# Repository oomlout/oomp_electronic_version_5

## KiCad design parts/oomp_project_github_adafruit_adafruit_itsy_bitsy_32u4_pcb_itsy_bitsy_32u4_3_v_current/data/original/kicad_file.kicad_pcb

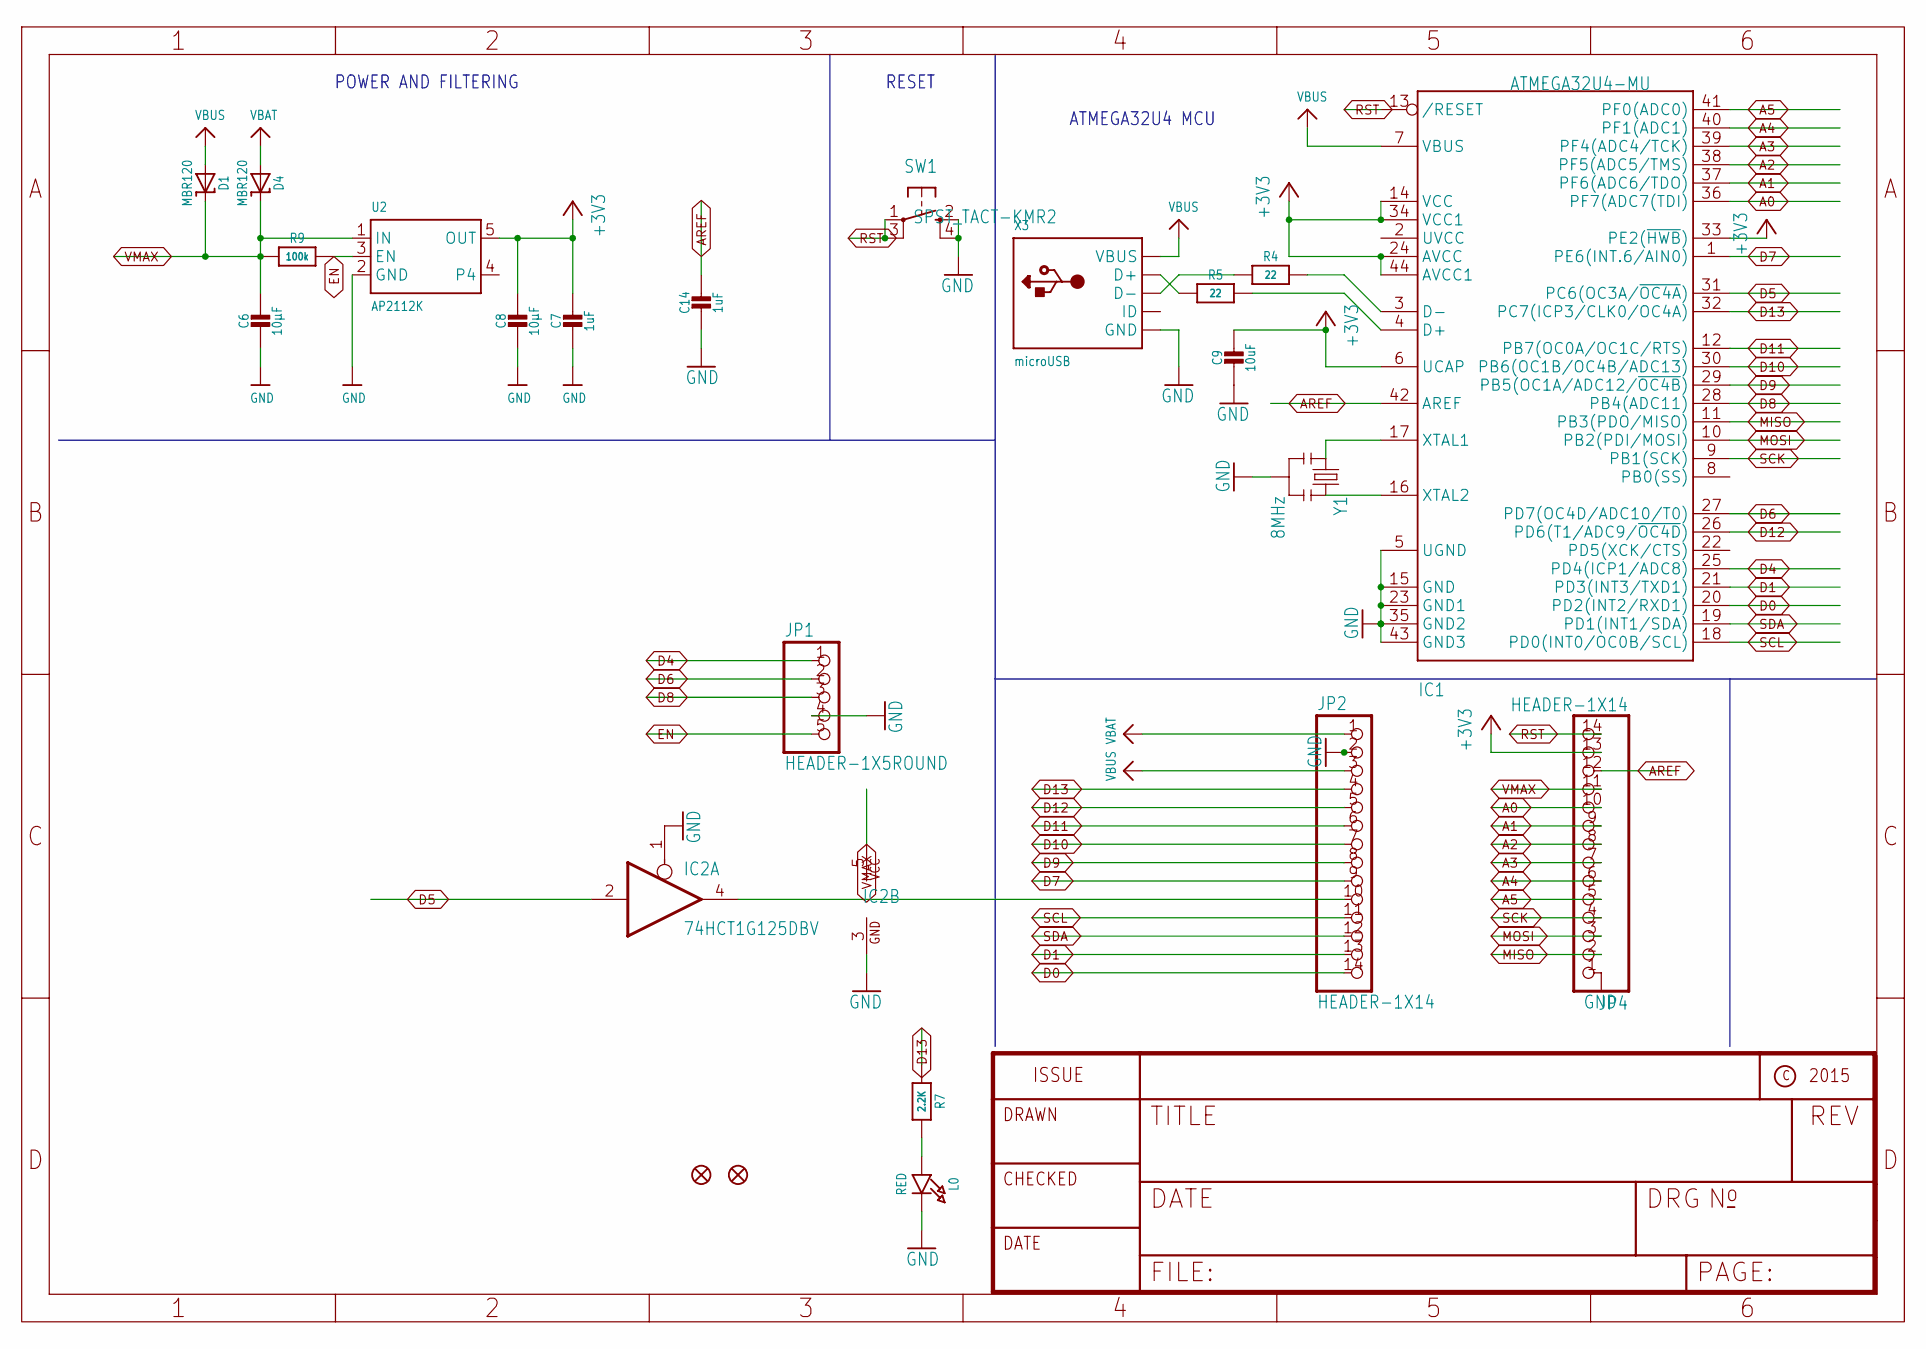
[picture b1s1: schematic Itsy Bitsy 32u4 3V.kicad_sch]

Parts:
C6, C8: 10µF; 0805-NO
C7, C14: 1uF; 0603-NO
C9: 10uF; 0805-NO
D1, D4: MBR120; SOD-123
IC1: ATMEGA32U4-MU; TQFN44_7MM
IC2: 74HCT1G125DBV; SOT23-5
JP1: HEADER-1X5ROUND; 1X05_ROUND
JP2, JP4: HEADER-1X14; 1X14_ROUND70
L0: RED; CHIPLED_0805_NOOUTLINE
R4, R5: 22; 0603-NO
R7: 2.2K; 0603-NO
R9: 100k; 0603-NO
SW1: SPST_TACT-KMR2; KMR2
U2: AP2112K; SOT23-5
U$34, U$35: FIDUCIAL""; FIDUCIAL_1MM
X3: microUSB; 4UCONN_20329_V2
Y1: 8MHz; RESONATOR-SMD

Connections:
+3V3: C7.1, C8.1, C9.1, IC1.6 (UCAP), IC1.14 (VCC), IC1.24 (AVCC), IC1.33 (PE2(~HWB)), IC1.34 (VCC1), IC1.44 (AVCC1), JP4.13, U2.5 (OUT)
A0: IC1.36 (PF7(ADC7(TDI)), JP4.10
A1: IC1.37 (PF6(ADC6/TDO)), JP4.9
A2: IC1.38 (PF5(ADC5/TMS)), JP4.8
A3: IC1.39 (PF4(ADC4/TCK)), JP4.7
A4: IC1.40 (PF1(ADC1)), JP4.6
A5: IC1.41 (PF0(ADC0)), JP4.5
AREF: C14.1, IC1.42 (AREF), JP4.12
D0: IC1.20 (PD2(INT2/RXD1)), JP2.14
D1: IC1.21 (PD3(INT3/TXD1)), JP2.13
D4: IC1.25 (PD4(ICP1/ADC8)), JP1.1
D5: IC1.31 (PC6(OC3A/~OC4A)), IC2.2 (I)
D5_OUT: IC2.4 (O), JP2.10
D6: IC1.27 (PD7(OC4D/ADC10/T0)), JP1.2
D7: IC1.1 (PE6(INT.6/AIN0)), JP2.9
D8: IC1.28 (PB4(ADC11)), JP1.3
D9: IC1.29 (PB5(OC1A/ADC12/~OC4B)), JP2.8
D10: IC1.30 (PB6(OC1B/OC4B/ADC13)), JP2.7
D11: IC1.12 (PB7(OC0A/OC1C/RTS)), JP2.6
D12: IC1.26 (PD6(T1/ADC9/~OC4D)), JP2.5
D13: IC1.32 (PC7(ICP3/CLK0/OC4A)), JP2.4, R7.1
D+: IC1.4 (D+), R5.2
D-: IC1.3 (D-), R4.2
EN: JP1.5, R9.2, U2.3 (EN)
GND: C6.2, C7.2, C8.2, C9.2, C14.2, IC1.5 (UGND), IC1.15 (GND), IC1.23 (GND1), IC1.35 (GND2), IC1.43 (GND3), IC2.1 (OE), IC2.3 (GND), JP1.4, JP2.2, JP4.1, L0.C, SW1.2 (S), SW1.4 (S1), U2.2 (GND), X3.BASE@1 (GND), X3.BASE@2 (GND), X3.GND, X3.SPRT@1 (GND), X3.SPRT@2 (GND), X3.SPRT@3 (GND), X3.SPRT@4 (GND), Y1.2
MISO: IC1.11 (PB3(PDO/MISO)), JP4.2
MOSI: IC1.10 (PB2(PDI/MOSI)), JP4.3
unnamed: L0.A, R7.2
unnamed: IC1.16 (XTAL2), Y1.3
unnamed: IC1.17 (XTAL1), Y1.1
unnamed: R5.1, X3.D+
unnamed: R4.1, X3.D-
RST: IC1.13 (/RESET), JP4.14, SW1.1, SW1.3 (P1)
SCK: IC1.9 (PB1(SCK)), JP4.4
SCL: IC1.18 (PD0(INT0/OC0B/SCL)), JP2.11
SDA: IC1.19 (PD1(INT1/SDA)), JP2.12
VBAT: D4.A, JP2.1
VBUS: D1.A, IC1.7 (VBUS), JP2.3, X3.VBUS
VMAX: C6.1, D1.C, D4.C, IC2.5 (VCC), JP4.11, R9.1, U2.1 (IN)

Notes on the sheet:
POWER AND FILTERING
RESET
ATMEGA32U4 MCU

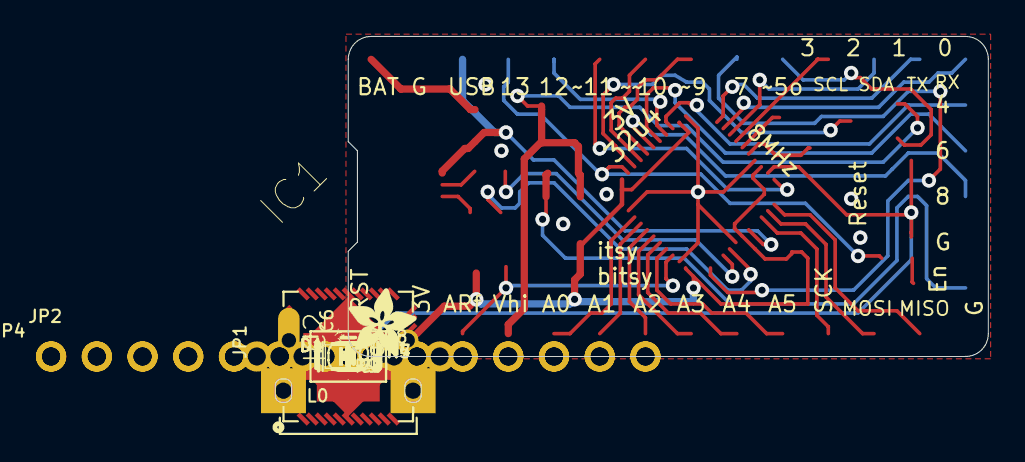
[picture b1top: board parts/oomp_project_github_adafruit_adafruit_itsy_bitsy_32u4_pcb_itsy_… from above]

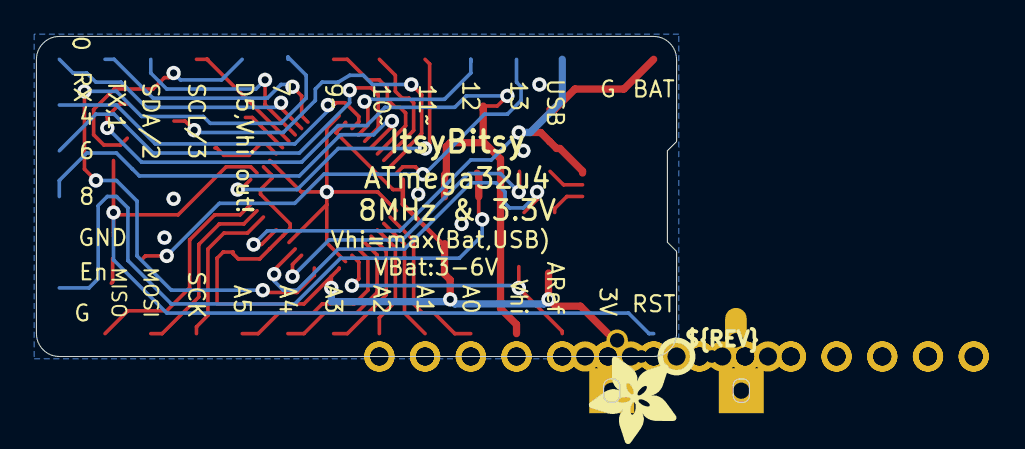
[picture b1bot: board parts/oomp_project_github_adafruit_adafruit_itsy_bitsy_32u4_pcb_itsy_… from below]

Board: 2 copper layers, 35.6 x 17.8 mm, 26 parts (2 on the bottom side), 39 nets.

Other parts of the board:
U$2: PCBFEAT-REV-040
U$4: ADAFRUIT_5MM
U$7: ADAFRUIT_3.5MM

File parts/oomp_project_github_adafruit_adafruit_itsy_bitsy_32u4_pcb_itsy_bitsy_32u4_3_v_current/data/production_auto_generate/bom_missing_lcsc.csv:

Designator,Comment,Footprint,OOMP ID,Reason
C6,10µF,Itsy Bitsy 32u4 3V-import-fps:0805-NO,electronic_capacitor_0805_10_micro_farad,No verified LCSC part number
C8,10µF,Itsy Bitsy 32u4 3V-import-fps:0805-NO,electronic_capacitor_0805_10_micro_farad,No verified LCSC part number
C9,10uF,Itsy Bitsy 32u4 3V-import-fps:0805-NO,electronic_capacitor_0805_10_micro_farad,No verified LCSC part number
D1,MBR120,Itsy Bitsy 32u4 3V-import-fps:SOD-123,,No verified LCSC part number
D4,MBR120,Itsy Bitsy 32u4 3V-import-fps:SOD-123,,No verified LCSC part number
IC1,ATMEGA32U4-MU,Itsy Bitsy 32u4 3V-import-fps:TQFN44_7MM,,No verified LCSC part number
IC2,74HCT1G125DBV,Itsy Bitsy 32u4 3V-import-fps:SOT23-5,,No verified LCSC part number
L0,RED,Itsy Bitsy 32u4 3V-import-fps:CHIPLED_0805_NOOUTLINE,electronic_led_0805_red,No verified LCSC part number
SW1,SPST_TACT-KMR2,Itsy Bitsy 32u4 3V-import-fps:KMR2,,No verified LCSC part number
U2,AP2112K,Itsy Bitsy 32u4 3V-import-fps:SOT23-5,,No verified LCSC part number
U$2,,Itsy Bitsy 32u4 3V-import-fps:PCBFEAT-REV-040,,No verified LCSC part number
U$4,,Itsy Bitsy 32u4 3V-import-fps:ADAFRUIT_5MM,,No verified LCSC part number
U$7,,Itsy Bitsy 32u4 3V-import-fps:ADAFRUIT_3.5MM,,No verified LCSC part number
U$34,"FIDUCIAL""""",Itsy Bitsy 32u4 3V-import-fps:FIDUCIAL_1MM,,No verified LCSC part number
U$35,"FIDUCIAL""""",Itsy Bitsy 32u4 3V-import-fps:FIDUCIAL_1MM,,No verified LCSC part number
X3,microUSB,Itsy Bitsy 32u4 3V-import-fps:4UCONN_20329_V2,,No verified LCSC part number
Y1,8MHz,Itsy Bitsy 32u4 3V-import-fps:RESONATOR-SMD,,No verified LCSC part number

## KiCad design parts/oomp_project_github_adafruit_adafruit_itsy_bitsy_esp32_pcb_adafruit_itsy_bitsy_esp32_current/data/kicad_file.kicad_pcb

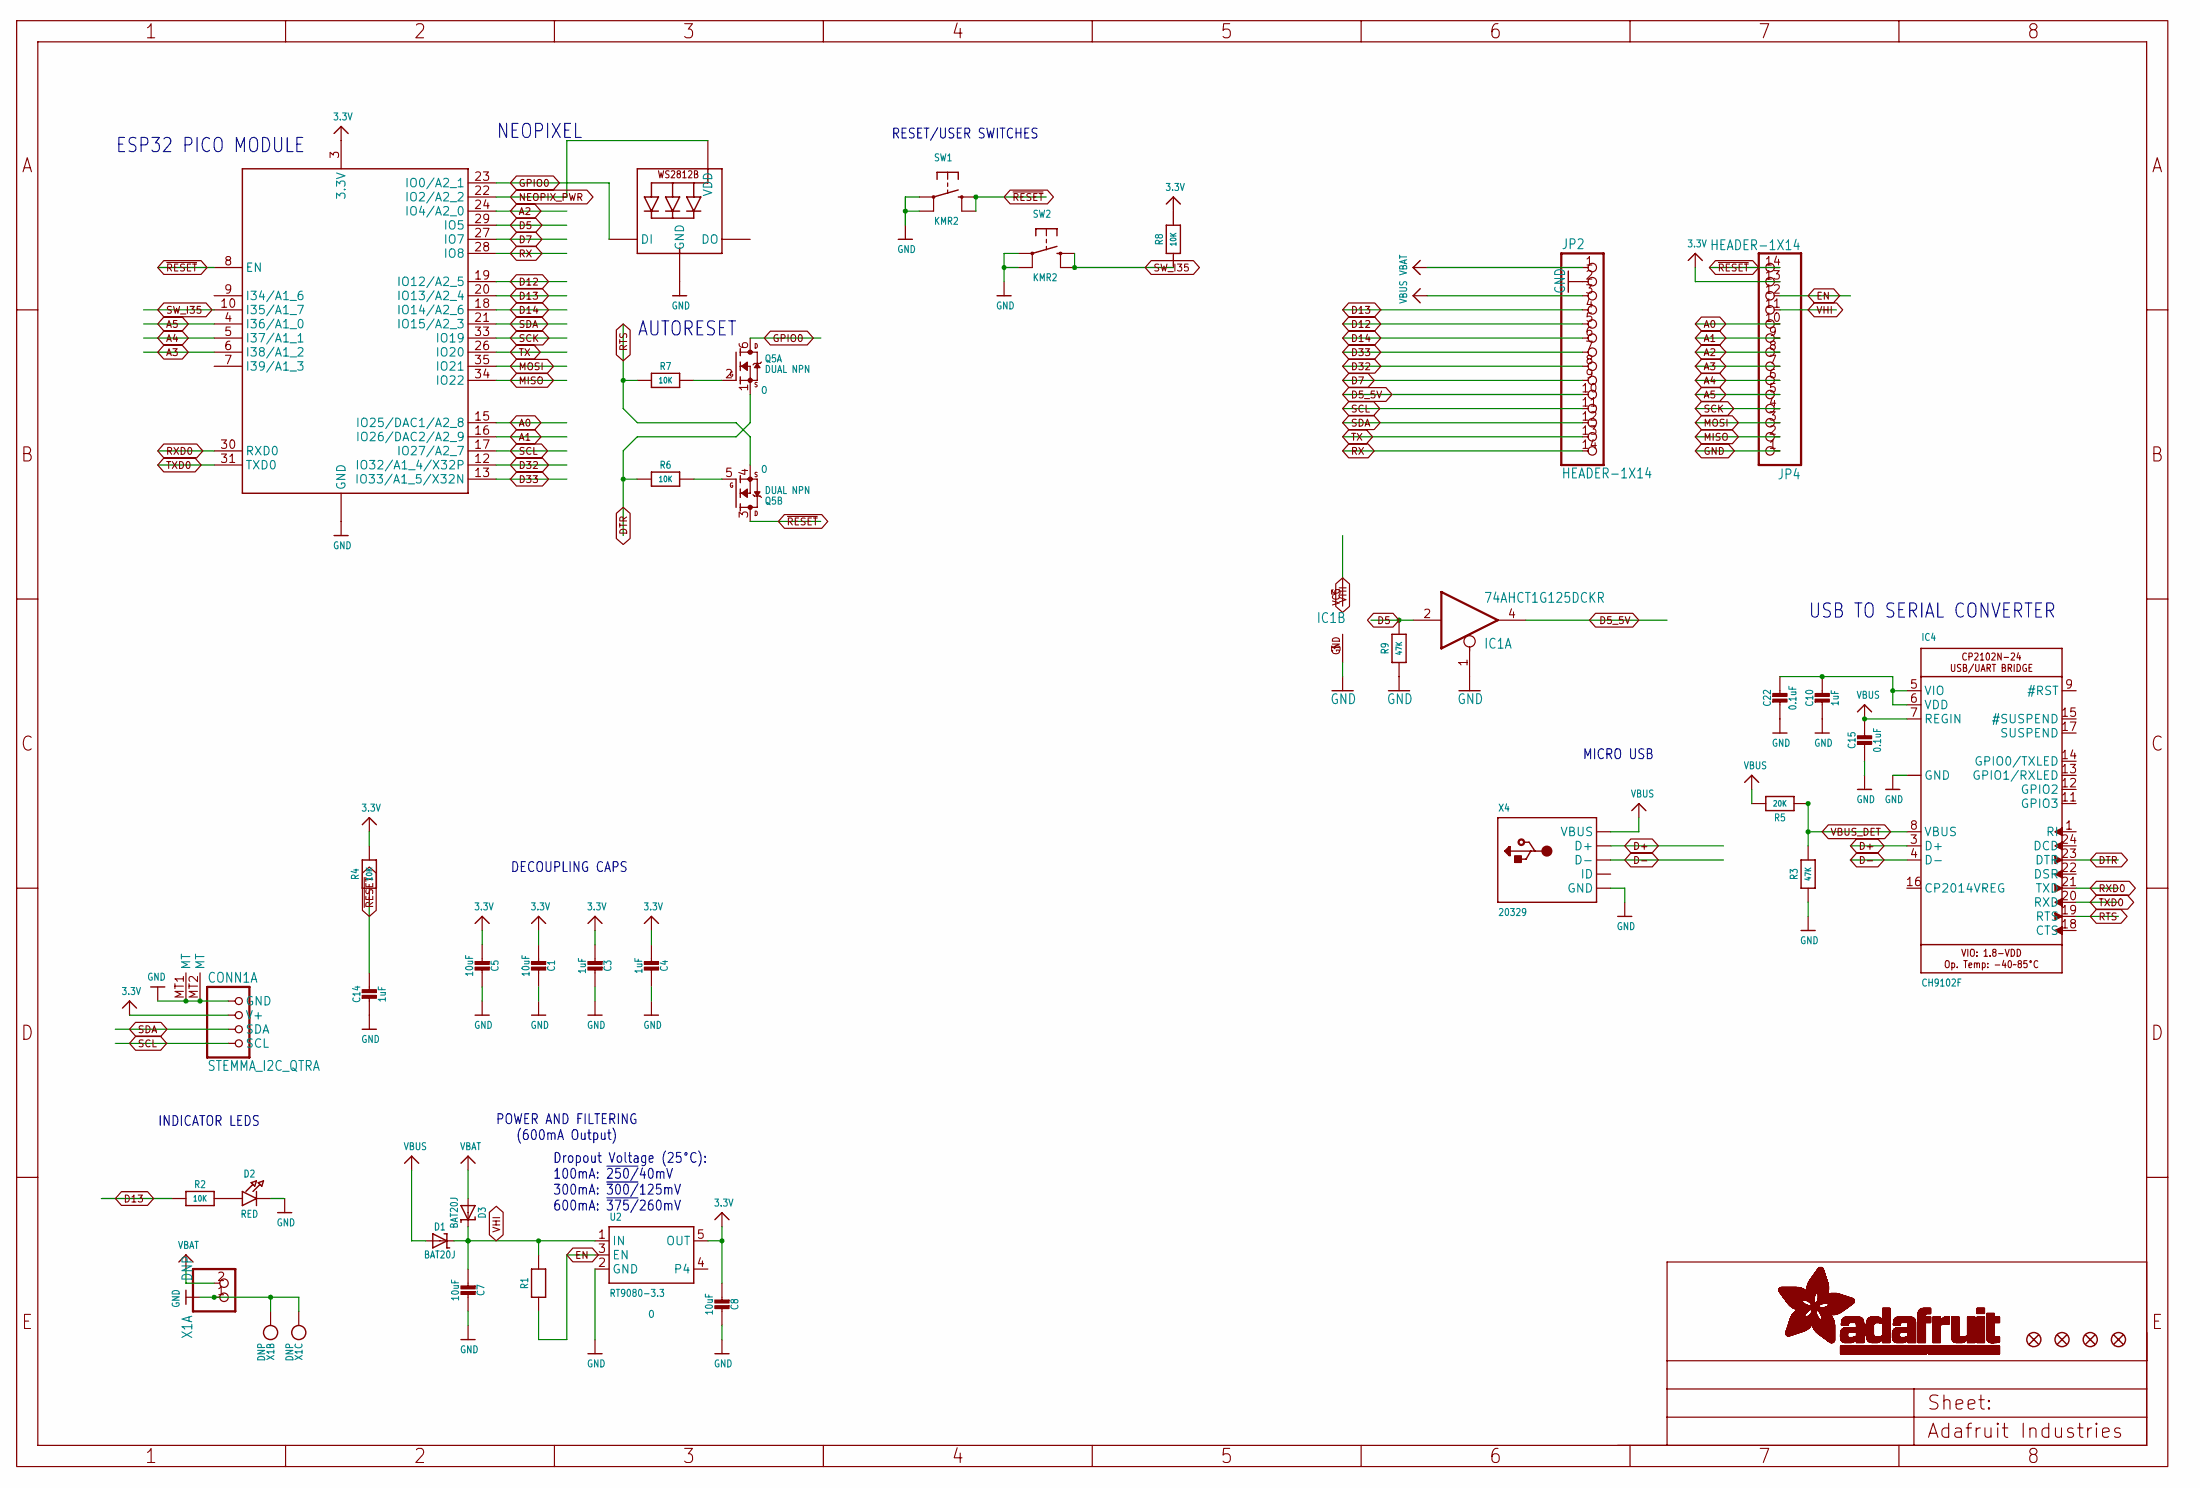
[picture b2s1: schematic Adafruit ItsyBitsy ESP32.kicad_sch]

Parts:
C1, C5, C7, C8: 10uF; 0805-NO
C3, C4, C10, C14: 1uF; 0603-NO
C15, C22: 0.1uF; 0603-NO
CONN1: STEMMA_I2C_QTRA; JST_SH4_RA; LCSC C145961
D1, D3: BAT20J; SOD-323
D2: RED; CHIPLED_0603_NOOUTLINE
FID1, FID2, FID3, FID4: FIDUCIAL_1MM
IC1: 74AHCT1G125DCKR; SC70-5
IC4: CH9102F; QFN24_4MM_SMSC; JLC_ROTATION 270
JP2, JP4: HEADER-1X14; 1X14_ROUND70
LED2: WS2812B_SK6805_1515; SK6805_1515; LCSC C2890035
Q5: DUAL NPN; SOT363; JLC_ROTATION 0
R1, R2, R4, R6, R7, R8: 10K; 0603-NO
R3, R9: 47K; 0603-NO
R5: 20K; 0603-NO
SW1, SW2: KMR2; BTN_RKB2_4.6X2.8
U2: RT9080-3.3; SOT23-5; JLC_ROTATION 0
X1: DNP; JSTPH2_BATT; LCSC C47647
X3: ESP32-PICO-MINI-02MINI; ESP32-PICO-MINI
X4: 20329; 4UCONN_20329_SLIM

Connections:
3.3V: C1.2, C3.2, C4.2, C5.2, C8.2, CONN1.2 (V+), JP4.13, R4.2, R8.2, U2.5 (OUT), X3.3 (3.3V)
3.45V: C10.1, C22.1, IC4.5 (VIO), IC4.6 (VDD)
A0: JP4.10, X3.15 (IO25/DAC1/A2_8)
A1: JP4.9, X3.16 (IO26/DAC2/A2_9)
A2: JP4.8, X3.24 (IO4/A2_0)
A3: JP4.7, X3.6 (I38/A1_2)
A4: JP4.6, X3.5 (I37/A1_1)
A5: JP4.5, X3.4 (I36/A1_0)
D5: IC1.2 (I), R9.2, X3.29 (IO5)
D5_5V: IC1.4 (O), JP2.10
D7: JP2.9, X3.27 (IO7)
D12: JP2.5, X3.19 (IO12/A2_5)
D13: JP2.4, R2.1, X3.20 (IO13/A2_4)
D14: JP2.6, X3.18 (IO14/A2_6)
D32: JP2.8, X3.12 (IO32/A1_4/X32P)
D33: JP2.7, X3.13 (IO33/A1_5/X32N)
D+: IC4.3 (D+), X4.D+
D-: IC4.4 (D-), X4.D-
DTR: IC4.23 (DTR), Q5.1 (S), R6.1
EN: JP4.12, R1.1, U2.3 (EN)
GND: C1.1, C3.1, C4.1, C5.1, C7.1, C8.1, C10.2, C14.2, C15.2, C22.2, CONN1.1 (GND), CONN1.MT1 (MT), CONN1.MT2 (MT), D2.C, IC1.1 (OE), IC1.3 (GND), IC4.2 (GND), IC4.THERM (GND), JP2.2, JP4.1, LED2.4 (GND), R3.1, R9.1, SW1.A, SW1.A' (P1), SW2.A, SW2.A' (P1), U2.2 (GND), X1.1, X1.NC1, X1.NC2, X3.1 (GND), X3.2 (GND), X3.11 (GND), X3.14 (GND), X3.36 (GND), X3.37 (GND), X3.38 (GND), X3.39 (GND), X3.40 (GND), X3.41 (GND), X3.42 (GND), X3.43 (GND), X3.44 (GND), X3.45 (GND), X3.46 (GND), X3.47 (GND), X3.48 (GND), X3.49 (GND), X3.50 (GND), X3.51 (GND), X3.52 (GND), X3.53 (GND), X3.54 (GND), X3.55 (GND), X3.56 (GND), X3.57 (GND), X3.58 (GND), X3.59 (GND), X3.60 (GND), X3.61 (GND), X4.BASE@1 (GND), X4.BASE@2 (GND), X4.GND, X4.SPRT@1 (GND), X4.SPRT@2 (GND), X4.SPRT@3 (GND), X4.SPRT@4 (GND)
GPIO0: LED2.1 (DI), Q5.6 (D), X3.23 (IO0/A2_1)
MISO: JP4.2, X3.34 (IO22)
MOSI: JP4.3, X3.35 (IO21)
unnamed: D2.A, R2.2
unnamed: Q5.5 (G), R6.2
unnamed: Q5.2 (G), R7.2
NEOPIX_PWR: LED2.2 (VDD), X3.22 (IO2/A2_2)
RTS: IC4.19 (RTS), Q5.4 (S), R7.1
RX: JP2.14, X3.28 (IO8)
RXD0: IC4.21 (TXD), X3.30 (RXD0)
SCK: JP4.4, X3.33 (IO19)
SCL: CONN1.4 (SCL), JP2.11, X3.17 (IO27/A2_7)
SDA: CONN1.3 (SDA), JP2.12, X3.21 (IO15/A2_3)
SW_I35: R8.1, SW2.B (S), SW2.B' (S1), X3.10 (I35/A1_7)
TX: JP2.13, X3.26 (IO20)
TXD0: IC4.20 (RXD), X3.31 (TXD0)
VBAT: D3.A, JP2.1, X1.2
VBUS: C15.1, D1.A, IC4.7 (REGIN), JP2.3, R5.2, X4.VBUS
VBUS_DET: IC4.8 (VBUS), R3.2, R5.1
VHI: C7.2, D1.C, D3.C, IC1.5 (VCC), JP4.11, R1.2, U2.1 (IN)
~RESET: C14.1, JP4.14, Q5.3 (D), R4.1, SW1.B (S), SW1.B' (S1), X3.8 (EN)

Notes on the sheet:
AUTORESET
MICRO USB
Dropout Voltage (25°C): 100mA: ~{250/}40mV 300mA: ~{300/}125mV 600mA: ~{375/}260mV
POWER AND FILTERING (600mA Output)
RESET/USER SWITCHES
ESP32 PICO MODULE
INDICATOR LEDS
DECOUPLING CAPS
USB TO SERIAL CONVERTER
NEOPIXEL

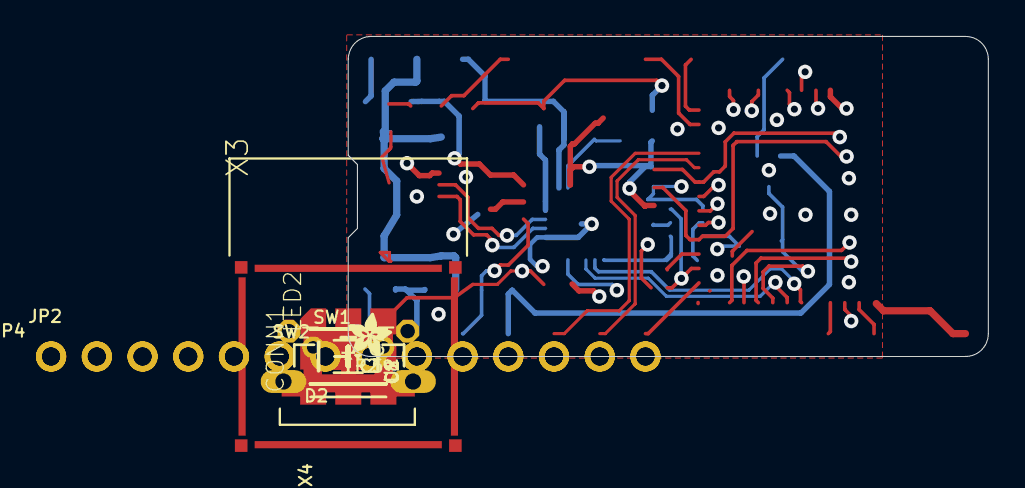
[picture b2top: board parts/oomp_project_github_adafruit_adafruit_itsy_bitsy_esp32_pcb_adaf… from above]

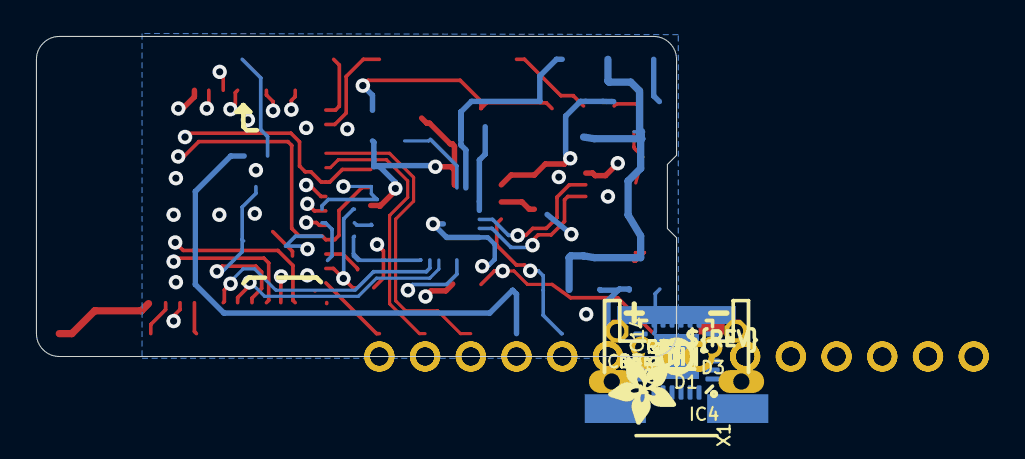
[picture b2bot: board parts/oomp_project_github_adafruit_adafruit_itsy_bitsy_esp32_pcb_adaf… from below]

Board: 4 copper layers, 35.6 x 17.8 mm, 87 parts (48 on the bottom side), 42 nets.

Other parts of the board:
E$1: ADAFRUIT_2.5MM
E$2: ADAFRUIT_3.5MM
PLABEL0: PLABEL0
PLABEL1: PLABEL1
PLABEL2: PLABEL2
PLABEL3: PLABEL3
PLABEL4: PLABEL4
PLABEL5: PLABEL5
PLABEL6: PLABEL6
PLABEL7: PLABEL7
PLABEL8: PLABEL8
PLABEL9: PLABEL9
PLABEL10: PLABEL10
PLABEL11: PLABEL11
PLABEL12: PLABEL12
PLABEL13: PLABEL13
PLABEL14: PLABEL14
PLABEL15: PLABEL15
PLABEL16: PLABEL16
PLABEL17: PLABEL17
PLABEL18: PLABEL18
PLABEL19: PLABEL19
PLABEL20: PLABEL20
PLABEL21: PLABEL21
PLABEL22: PLABEL22
PLABEL23: PLABEL23
PLABEL24: PLABEL24
PLABEL25: PLABEL25
PLABEL26: PLABEL26
PLABEL27: PLABEL27
PLABEL28: PLABEL28
PLABEL29: PLABEL29
PLABEL30: PLABEL30
PLABEL31: PLABEL31
PLABEL32: PLABEL32
PLABEL33: PLABEL33
PLABEL34: PLABEL34
PLABEL35: PLABEL35
PLABEL36: PLABEL36
PLABEL37: PLABEL37
PLABEL38: PLABEL38
PLABEL39: PLABEL39
PLABEL40: PLABEL40
PLABEL41: PLABEL41
PLABEL42: PLABEL42
PLABEL43: PLABEL43
PLABEL44: PLABEL44
U$16: PCBFEAT-REV-040

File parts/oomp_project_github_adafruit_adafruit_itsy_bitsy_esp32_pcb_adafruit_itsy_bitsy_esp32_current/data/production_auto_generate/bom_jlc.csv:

Comment,Designator,Footprint,LCSC Part #
,"JP2,JP4",Adafruit ItsyBitsy ESP32-import-fps:1X14_ROUND70,C2905490
,E$1,Adafruit ItsyBitsy ESP32-import-fps:ADAFRUIT_2.5MM,
,E$2,Adafruit ItsyBitsy ESP32-import-fps:ADAFRUIT_3.5MM,
,U$16,Adafruit ItsyBitsy ESP32-import-fps:PCBFEAT-REV-040,
,PLABEL0,Adafruit ItsyBitsy ESP32-import-fps:PLABEL0,
,PLABEL1,Adafruit ItsyBitsy ESP32-import-fps:PLABEL1,
,PLABEL10,Adafruit ItsyBitsy ESP32-import-fps:PLABEL10,
,PLABEL11,Adafruit ItsyBitsy ESP32-import-fps:PLABEL11,
,PLABEL12,Adafruit ItsyBitsy ESP32-import-fps:PLABEL12,
,PLABEL13,Adafruit ItsyBitsy ESP32-import-fps:PLABEL13,
,PLABEL14,Adafruit ItsyBitsy ESP32-import-fps:PLABEL14,
,PLABEL15,Adafruit ItsyBitsy ESP32-import-fps:PLABEL15,
,PLABEL16,Adafruit ItsyBitsy ESP32-import-fps:PLABEL16,
,PLABEL17,Adafruit ItsyBitsy ESP32-import-fps:PLABEL17,
,PLABEL18,Adafruit ItsyBitsy ESP32-import-fps:PLABEL18,
,PLABEL19,Adafruit ItsyBitsy ESP32-import-fps:PLABEL19,
,PLABEL2,Adafruit ItsyBitsy ESP32-import-fps:PLABEL2,
,PLABEL20,Adafruit ItsyBitsy ESP32-import-fps:PLABEL20,
,PLABEL21,Adafruit ItsyBitsy ESP32-import-fps:PLABEL21,
,PLABEL22,Adafruit ItsyBitsy ESP32-import-fps:PLABEL22,
,PLABEL23,Adafruit ItsyBitsy ESP32-import-fps:PLABEL23,
,PLABEL24,Adafruit ItsyBitsy ESP32-import-fps:PLABEL24,
,PLABEL25,Adafruit ItsyBitsy ESP32-import-fps:PLABEL25,
,PLABEL26,Adafruit ItsyBitsy ESP32-import-fps:PLABEL26,
,PLABEL27,Adafruit ItsyBitsy ESP32-import-fps:PLABEL27,
,PLABEL28,Adafruit ItsyBitsy ESP32-import-fps:PLABEL28,
,PLABEL29,Adafruit ItsyBitsy ESP32-import-fps:PLABEL29,
,PLABEL3,Adafruit ItsyBitsy ESP32-import-fps:PLABEL3,
,PLABEL30,Adafruit ItsyBitsy ESP32-import-fps:PLABEL30,
,PLABEL31,Adafruit ItsyBitsy ESP32-import-fps:PLABEL31,
,PLABEL32,Adafruit ItsyBitsy ESP32-import-fps:PLABEL32,
,PLABEL33,Adafruit ItsyBitsy ESP32-import-fps:PLABEL33,
,PLABEL34,Adafruit ItsyBitsy ESP32-import-fps:PLABEL34,
,PLABEL35,Adafruit ItsyBitsy ESP32-import-fps:PLABEL35,
,PLABEL36,Adafruit ItsyBitsy ESP32-import-fps:PLABEL36,
,PLABEL37,Adafruit ItsyBitsy ESP32-import-fps:PLABEL37,
,PLABEL38,Adafruit ItsyBitsy ESP32-import-fps:PLABEL38,
,PLABEL39,Adafruit ItsyBitsy ESP32-import-fps:PLABEL39,
,PLABEL4,Adafruit ItsyBitsy ESP32-import-fps:PLABEL4,
,PLABEL40,Adafruit ItsyBitsy ESP32-import-fps:PLABEL40,
,PLABEL41,Adafruit ItsyBitsy ESP32-import-fps:PLABEL41,
,PLABEL42,Adafruit ItsyBitsy ESP32-import-fps:PLABEL42,
,PLABEL43,Adafruit ItsyBitsy ESP32-import-fps:PLABEL43,
,PLABEL44,Adafruit ItsyBitsy ESP32-import-fps:PLABEL44,
,PLABEL5,Adafruit ItsyBitsy ESP32-import-fps:PLABEL5,
,PLABEL6,Adafruit ItsyBitsy ESP32-import-fps:PLABEL6,
,PLABEL7,Adafruit ItsyBitsy ESP32-import-fps:PLABEL7,
,PLABEL8,Adafruit ItsyBitsy ESP32-import-fps:PLABEL8,
,PLABEL9,Adafruit ItsyBitsy ESP32-import-fps:PLABEL9,
0.1uF,"C15,C22",Adafruit ItsyBitsy ESP32-import-fps:0603-NO,C14663
10K,"R1,R2,R4,R6,R7,R8",Adafruit ItsyBitsy ESP32-import-fps:0603-NO,C98220
10uF,"C1,C5,C7,C8",Adafruit ItsyBitsy ESP32-import-fps:0805-NO,
1uF,"C3,C4,C10,C14",Adafruit ItsyBitsy ESP32-import-fps:0603-NO,C5673
20329,X4,Adafruit ItsyBitsy ESP32-import-fps:4UCONN_20329_SLIM,
20K,R5,Adafruit ItsyBitsy ESP32-import-fps:0603-NO,
47K,"R3,R9",Adafruit ItsyBitsy ESP32-import-fps:0603-NO,C2907042
74AHCT1G125DCKR,IC1,Adafruit ItsyBitsy ESP32-import-fps:SC70-5,
BAT20J,"D1,D3",Adafruit ItsyBitsy ESP32-import-fps:SOD-323,
CH9102F,IC4,Adafruit ItsyBitsy ESP32-import-fps:QFN24_4MM_SMSC,
DNP,X1,Adafruit ItsyBitsy ESP32-import-fps:JSTPH2_BATT,
DUAL NPN,Q5,Adafruit ItsyBitsy ESP32-import-fps:SOT363,
ESP32-PICO-MINI-02MINI,X3,Adafruit ItsyBitsy ESP32-import-fps:ESP32-PICO-MINI,
KMR2,"SW1,SW2",Adafruit ItsyBitsy ESP32-import-fps:BTN_RKB2_4.6X2.8,
RED,D2,Adafruit ItsyBitsy ESP32-import-fps:CHIPLED_0603_NOOUTLINE,
RT9080-3.3,U2,Adafruit ItsyBitsy ESP32-import-fps:SOT23-5,
STEMMA_I2C_QTRA,CONN1,Adafruit ItsyBitsy ESP32-import-fps:JST_SH4_RA,
WS2812B_SK6805_1515,LED2,Adafruit ItsyBitsy ESP32-import-fps:SK6805_1515,

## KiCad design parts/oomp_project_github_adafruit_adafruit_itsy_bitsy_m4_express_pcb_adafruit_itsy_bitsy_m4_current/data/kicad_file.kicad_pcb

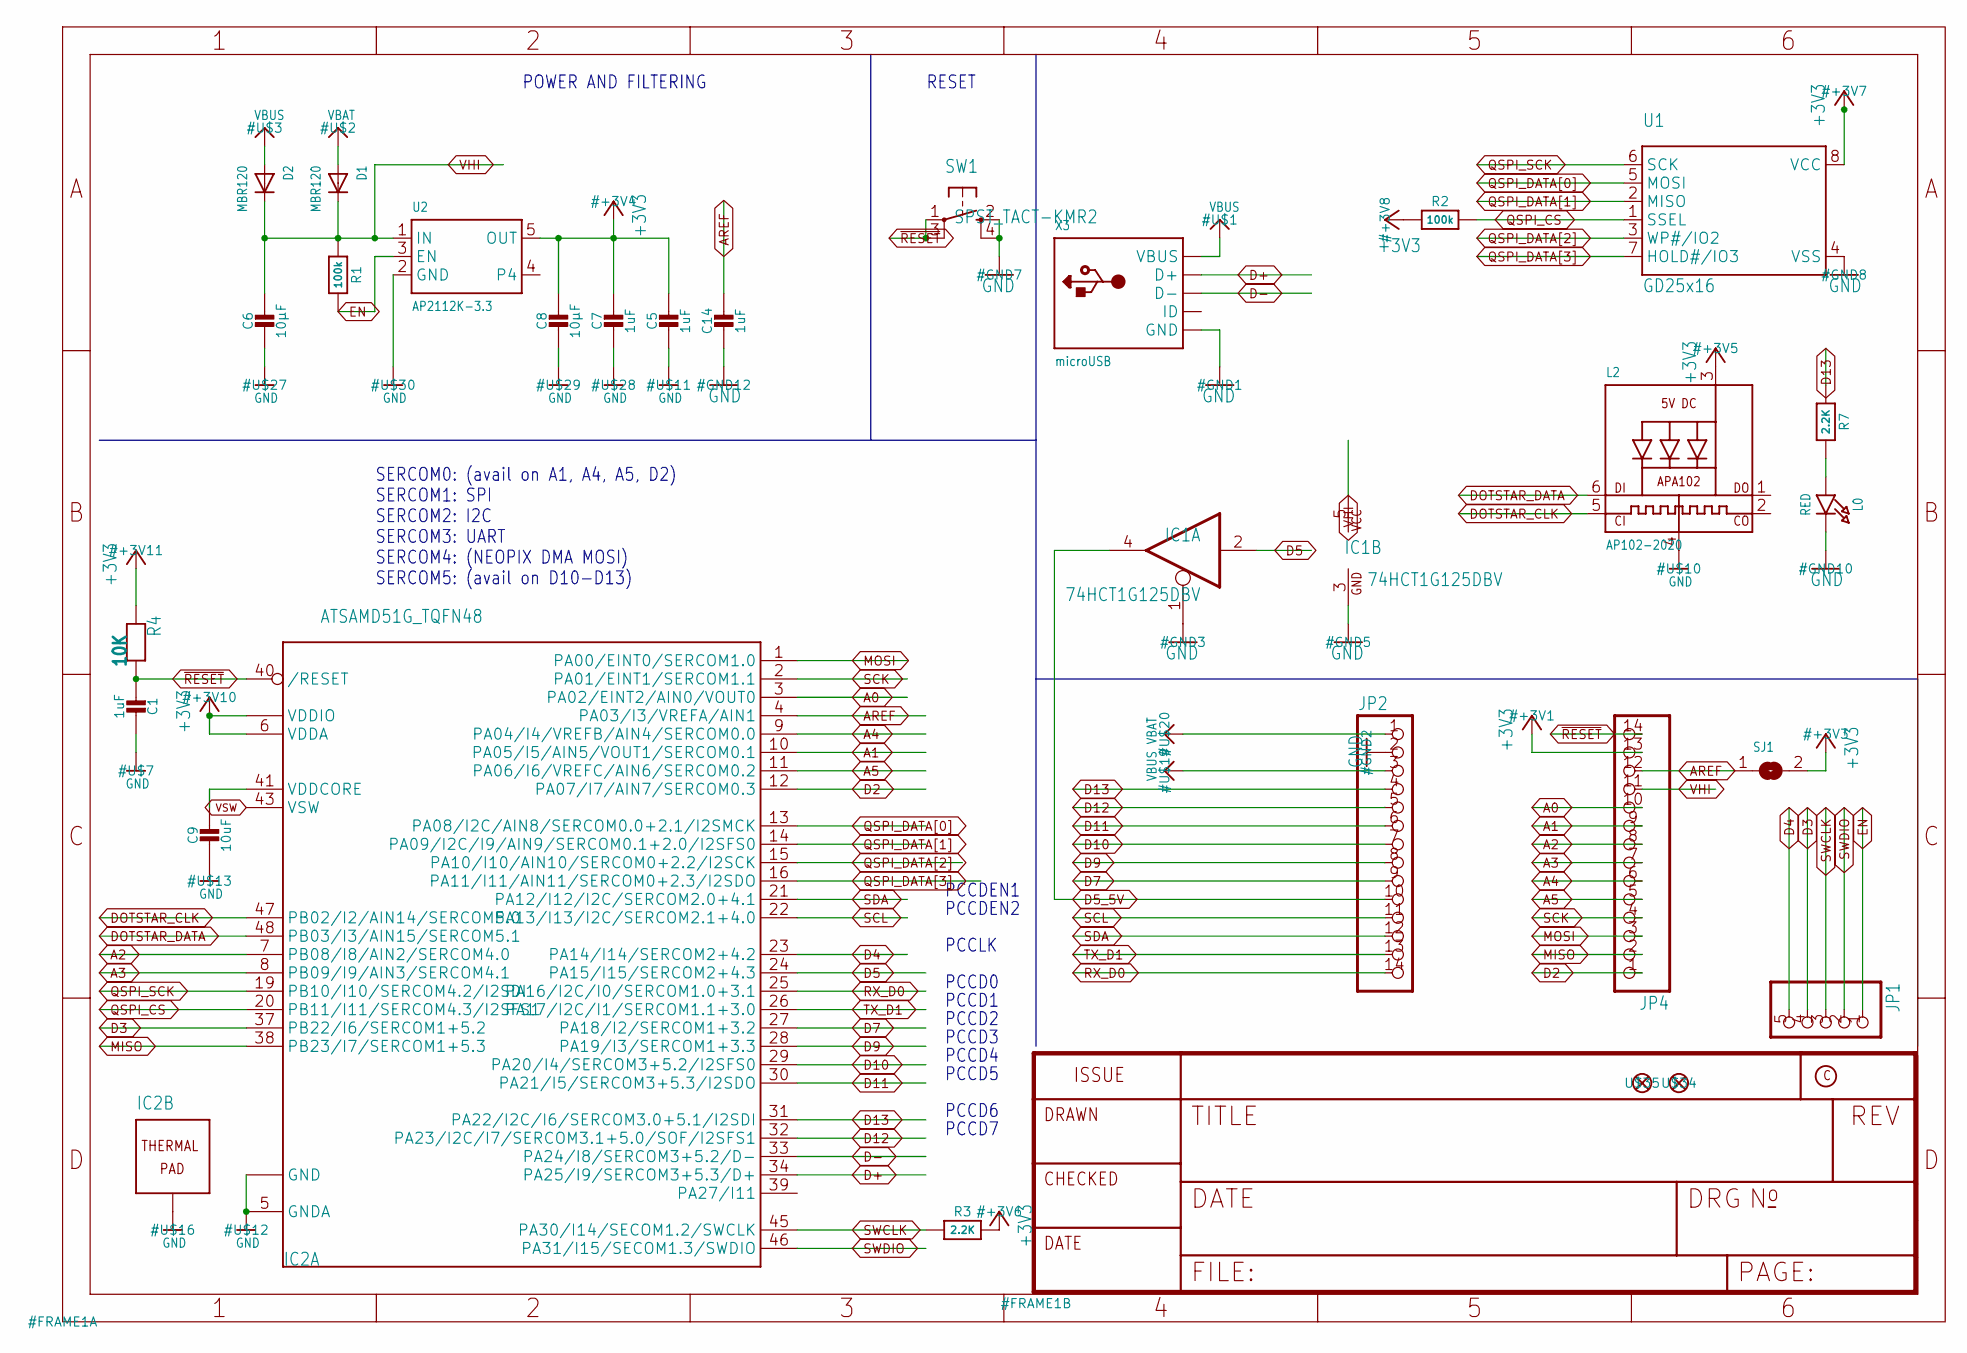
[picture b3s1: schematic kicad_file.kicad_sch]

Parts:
C1: 1uF; _0603MP
C5, C7, C14: 1uF; 0603-NO
C6, C8: 10µF; 0805-NO
C9: 10uF; _0805MP
D1, D2: MBR120; SOD-123FL
IC1: 74HCT1G125DBV; SOT23-5
IC2: ATSAMD51G_TQFN48; TQFN48_7MM
JP1: HEADER-1X570MIL; 1X05_ROUND_70
JP2, JP4: HEADER-1X14; 1X14_ROUND70
L0: RED; CHIPLED_0603_NOOUTLINE
L2: AP102-2020; APA102_2020
R1, R2: 100k; 0603-NO
R3: 2.2K; _0603MP
R4: 10K; _0603MP
R7: 2.2K; 0603-NO
SJ1: SOLDERJUMPERCLOSED; SOLDERJUMPER_CLOSEDWIRE
SW1: SPST_TACT-KMR2; KMR2
U1: GD25x16; USON8
U2: AP2112K-3.3; SOT23-5
U$34, U$35: FIDUCIAL_1MM
X3: microUSB; 4UCONN_20329_V2

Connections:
+3V3: C5.1, C7.1, C8.1, IC2.6 (VDDA), IC2.17 (VDDIO), IC2.36 (VDDIO), IC2.44 (VDDIO), JP4.13, L2.3 (VDD), R2.1, R3.2, R4.1, SJ1.2, U1.8 (VCC), U2.5 (OUT)
A0: IC2.3 (PA02/EINT2/AIN0/VOUT0), JP4.10
A1: IC2.10 (PA05/I5/AIN5/VOUT1/SERCOM0.1), JP4.9
A2: IC2.7 (PB08/I8/AIN2/SERCOM4.0), JP4.8
A3: IC2.8 (PB09/I9/AIN3/SERCOM4.1), JP4.7
A4: IC2.9 (PA04/I4/VREFB/AIN4/SERCOM0.0), JP4.6
A5: IC2.11 (PA06/I6/VREFC/AIN6/SERCOM0.2), JP4.5
AREF: C14.1, IC2.4 (PA03/I3/VREFA/AIN1), JP4.12, SJ1.1
D2: IC2.12 (PA07/I7/AIN7/SERCOM0.3), JP4.1
D3: IC2.37 (PB22/I6/SERCOM1+5.2), JP1.4
D4: IC2.23 (PA14/I14/SERCOM2+4.2), JP1.5
D5: IC1.2 (I), IC2.24 (PA15/I15/SERCOM2+4.3)
D5_5V: IC1.4 (O), JP2.10
D7: IC2.27 (PA18/I2/SERCOM1+3.2), JP2.9
D9: IC2.28 (PA19/I3/SERCOM1+3.3), JP2.8
D10: IC2.29 (PA20/I4/SERCOM3+5.2/I2SFS0), JP2.7
D11: IC2.30 (PA21/I5/SERCOM3+5.3/I2SDO), JP2.6
D12: IC2.32 (PA23/I2C/I7/SERCOM3.1+5.0/SOF/I2SFS1), JP2.5
D13: IC2.31 (PA22/I2C/I6/SERCOM3.0+5.1/I2SDI), JP2.4, R7.1
D+: IC2.34 (PA25/I9/SERCOM3+5.3/D+), X3.D+
D-: IC2.33 (PA24/I8/SERCOM3+5.2/D-), X3.D-
DOTSTAR_CLK: IC2.47 (PB02/I2/AIN14/SERCOM5.0), L2.5 (CKI)
DOTSTAR_DATA: IC2.48 (PB03/I3/AIN15/SERCOM5.1), L2.6 (DI)
EN: JP1.1, R1.2, U2.3 (EN)
GND: C1.1, C5.2, C6.2, C7.2, C8.2, C9.2, C14.2, IC1.1 (OE), IC1.3 (GND), IC2.5 (GNDA), IC2.18 (GND), IC2.35 (GND), IC2.42 (GND), IC2.THERMAL (TP), JP2.2, L0.C, L2.4 (GND), SW1.2 (S), SW1.4 (S1), U1.4 (VSS), U2.2 (GND), X3.BASE@1 (GND), X3.BASE@2 (GND), X3.GND, X3.SPRT@1 (GND), X3.SPRT@2 (GND), X3.SPRT@3 (GND), X3.SPRT@4 (GND)
MISO: IC2.38 (PB23/I7/SERCOM1+5.3), JP4.2
MOSI: IC2.1 (PA00/EINT0/SERCOM1.0), JP4.3
unnamed: L0.A, R7.2
QSPI_CS: IC2.20 (PB11/I11/SERCOM4.3/I2SFS1), R2.2, U1.1 (SSEL)
QSPI_DATA[0]: IC2.13 (PA08/I2C/AIN8/SERCOM0.0+2.1/I2SMCK), U1.5 (MOSI)
QSPI_DATA[1]: IC2.14 (PA09/I2C/I9/AIN9/SERCOM0.1+2.0/I2SFS0), U1.2 (MISO)
QSPI_DATA[2]: IC2.15 (PA10/I10/AIN10/SERCOM0+2.2/I2SCK), U1.3 (WP#/IO2)
QSPI_DATA[3]: IC2.16 (PA11/I11/AIN11/SERCOM0+2.3/I2SDO), U1.7 (HOLD#/IO3)
QSPI_SCK: IC2.19 (PB10/I10/SERCOM4.2/I2SDI), U1.6 (SCK)
RX_D0: IC2.25 (PA16/I2C/I0/SERCOM1.0+3.1), JP2.14
SCK: IC2.2 (PA01/EINT1/SERCOM1.1), JP4.4
SCL: IC2.22 (PA13/I13/I2C/SERCOM2.1+4.0), JP2.11
SDA: IC2.21 (PA12/I12/I2C/SERCOM2.0+4.1), JP2.12
SWCLK: IC2.45 (PA30/I14/SECOM1.2/SWCLK), JP1.3, R3.1
SWDIO: IC2.46 (PA31/I15/SECOM1.3/SWDIO), JP1.2
TX_D1: IC2.26 (PA17/I2C/I1/SERCOM1.1+3.0), JP2.13
VBAT: D1.A, JP2.1
VBUS: D2.A, JP2.3, X3.VBUS
VDDCORE: C9.1, IC2.41 (VDDCORE)
VHI: C6.1, D1.C, D2.C, IC1.5 (VCC), JP4.11, R1.1, U2.1 (IN)
VSW: IC2.43 (VSW)
~RESET: C1.2, IC2.40 (/RESET), JP4.14, R4.2, SW1.1, SW1.3 (P1)

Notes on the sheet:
PCCD2
PCCLK
SERCOM0: (avail on A1, A4, A5, D2) SERCOM1: SPI SERCOM2: I2C SERCOM3: UART SERCOM4: (NEOPIX DMA MOSI) SERCOM5: (avail on D10-D13)
PCCD7
PCCDEN1
RESET
PCCD5
PCCD4
PCCD0
PCCD3
PCCD6
POWER AND FILTERING
PCCD1
PCCDEN2

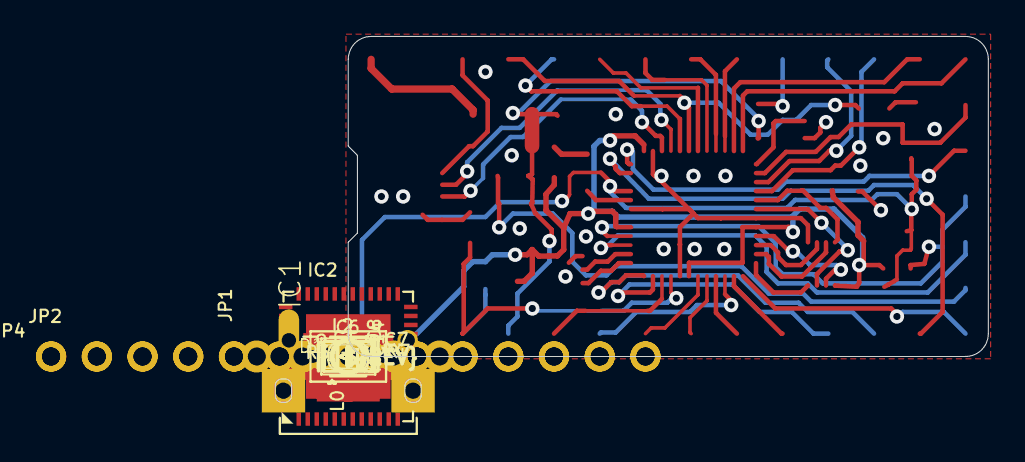
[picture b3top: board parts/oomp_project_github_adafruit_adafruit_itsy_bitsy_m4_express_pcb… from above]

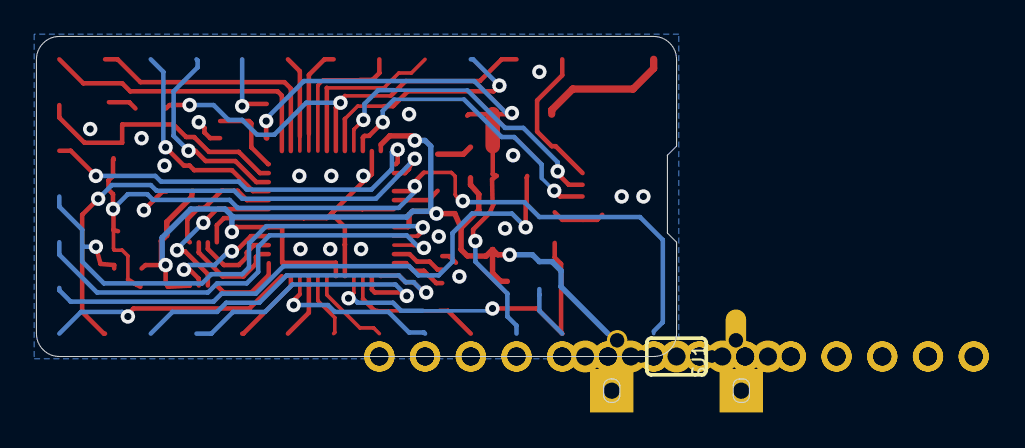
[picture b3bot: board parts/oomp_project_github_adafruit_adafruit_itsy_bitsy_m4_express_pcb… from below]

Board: 4 copper layers, 35.6 x 17.8 mm, 31 parts (2 on the bottom side), 46 nets.

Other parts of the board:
U$4: ITSYM4_TOP
U$5: ITSYM4_BOT
U$6: PCBFEAT-REV-040

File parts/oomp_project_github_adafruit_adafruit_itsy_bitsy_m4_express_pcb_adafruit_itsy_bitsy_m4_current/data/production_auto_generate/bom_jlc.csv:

Comment,Designator,Footprint,LCSC Part #
,JP1,Adafruit ItsyBitsy M4-import-fps:1X05_ROUND_70,C42431835
,"JP2,JP4",Adafruit ItsyBitsy M4-import-fps:1X14_ROUND70,C2905490
,U$5,Adafruit ItsyBitsy M4-import-fps:ITSYM4_BOT,
,U$4,Adafruit ItsyBitsy M4-import-fps:ITSYM4_TOP,
,U$6,Adafruit ItsyBitsy M4-import-fps:PCBFEAT-REV-040,
100k,"R1,R2",Adafruit ItsyBitsy M4-import-fps:0603-NO,C25803
10K,R4,Adafruit ItsyBitsy M4-import-fps:_0603MP,C98220
10uF,C9,Adafruit ItsyBitsy M4-import-fps:_0805MP,
10µF,"C6,C8",Adafruit ItsyBitsy M4-import-fps:0805-NO,
1uF,"C5,C7,C14",Adafruit ItsyBitsy M4-import-fps:0603-NO,C5673
1uF,C1,Adafruit ItsyBitsy M4-import-fps:_0603MP,C5673
2.2K,R7,Adafruit ItsyBitsy M4-import-fps:0603-NO,C4190
2.2K,R3,Adafruit ItsyBitsy M4-import-fps:_0603MP,C4190
74HCT1G125DBV,IC1,Adafruit ItsyBitsy M4-import-fps:SOT23-5,
AP102-2020,L2,Adafruit ItsyBitsy M4-import-fps:APA102_2020,
AP2112K-3.3,U2,Adafruit ItsyBitsy M4-import-fps:SOT23-5,
ATSAMD51G_TQFN48,IC2,Adafruit ItsyBitsy M4-import-fps:TQFN48_7MM,
FIDUCIAL_1MM,"U$34,U$35",Adafruit ItsyBitsy M4-import-fps:FIDUCIAL_1MM,
GD25x16,U1,Adafruit ItsyBitsy M4-import-fps:USON8,
MBR120,"D1,D2",Adafruit ItsyBitsy M4-import-fps:SOD-123FL,
microUSB,X3,Adafruit ItsyBitsy M4-import-fps:4UCONN_20329_V2,
RED,L0,Adafruit ItsyBitsy M4-import-fps:CHIPLED_0603_NOOUTLINE,
SPST_TACT-KMR2,SW1,Adafruit ItsyBitsy M4-import-fps:KMR2,
